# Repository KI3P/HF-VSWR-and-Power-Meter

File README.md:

# HF-VSWR-and-Power-Meter

System that measures the VSWR and power level of transmitter signals in the HF bands (3.5 MHz to 30 MHz) with better than 5% accuracy for VSWRs below 3.0. For a detailed explanation of its operation, see [its project page](https://ko4thb.github.io/2023/12/23/vswr_and_power_meter.html).

Gerbers were generated for manufacture by JLCPCB.

Credit: thanks to [G3TXQ](http://karinya.net/g3txq/swr_meter/) for sharing his SWR meter design and [schematic diagram](http://karinya.net/g3txq/swr_meter/schematic.jpg). Thanks to N7DDC for sharing the design of the [ATU-100 antenna tuner](https://github.com/Dfinitski/N7DDC-ATU-100-mini-and-extended-boards). And to W2AEW for his [excellent explanation](https://www.youtube.com/watch?v=byF1FLdbUiA) of how a directional coupler works. IN3OTD has an [online calculator](https://www.qsl.net/in3otd/parallr.html) for synthesizing arbitrary resistor values from standard value.  All these were tremendously helpful as I designed this VSWR meter.

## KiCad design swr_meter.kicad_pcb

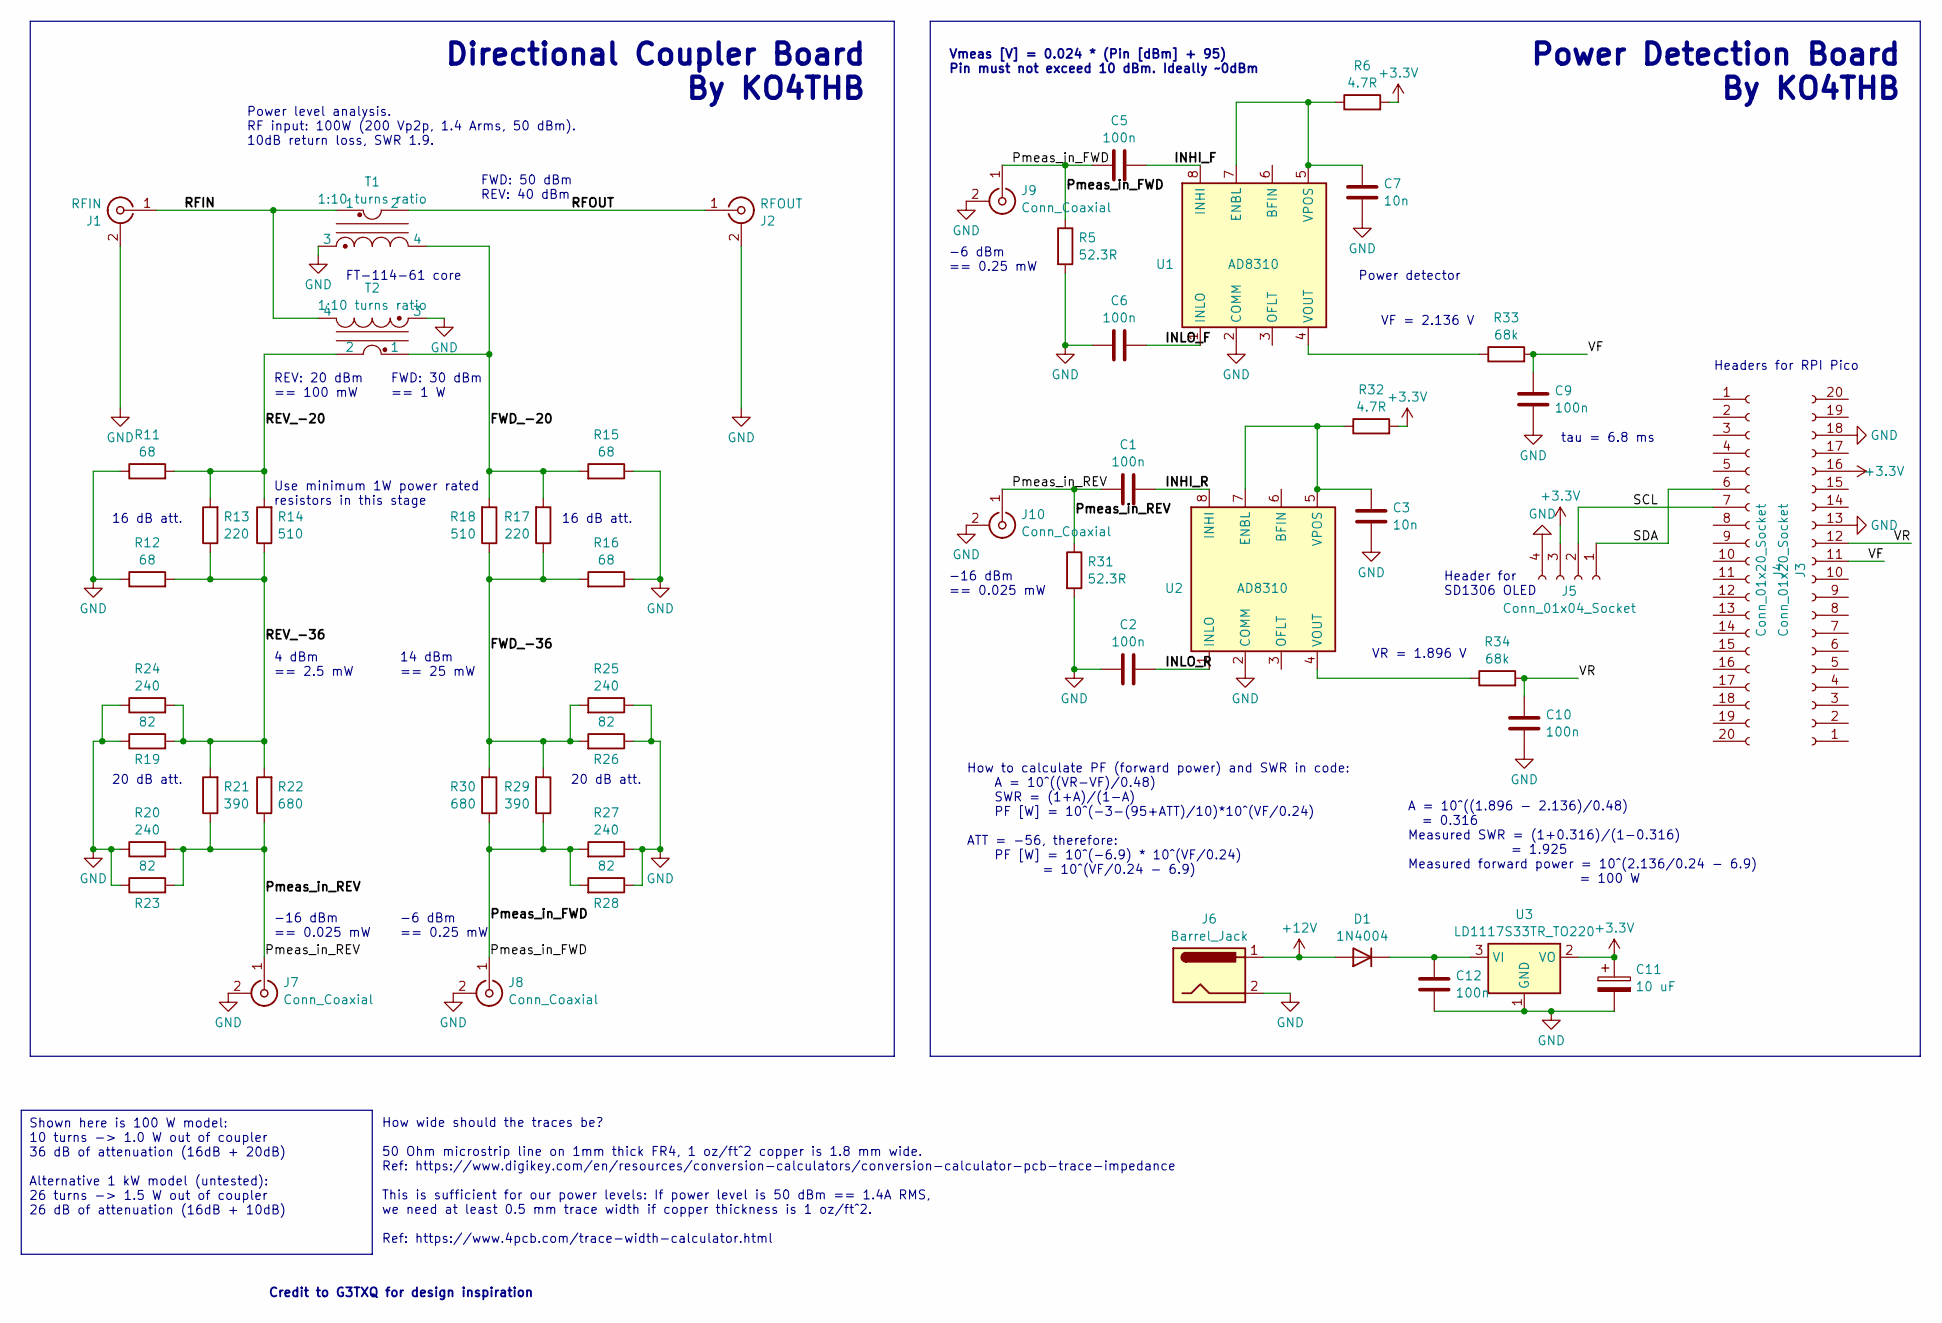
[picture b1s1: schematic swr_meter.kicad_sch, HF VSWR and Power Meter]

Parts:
C1, C2, C5, C6, C9, C10, C12: 100n; C_Disc_D9.0mm_W2.5mm_P5.00mm
C3, C7: 10n; C_Disc_D9.0mm_W2.5mm_P5.00mm
C11: 10 uF; CP_Radial_D6.3mm_P2.50mm
D1: 1N4004; D_DO-41_SOD81_P10.16mm_Horizontal
J1: RFIN; BNC_TEConnectivity_1478035_Horizontal
J2: RFOUT; BNC_TEConnectivity_1478035_Horizontal
J3, J4: Conn_01x20_Socket; PinHeader_1x20_P2.54mm_Vertical
J5: Conn_01x04_Socket; PinHeader_1x04_P2.54mm_Vertical
J6: Barrel_Jack; BarrelJack_Wuerth_6941xx301002
J7, J8, J9, J10: Conn_Coaxial; SMA_Amphenol_901-144_Vertical
R5, R31: 52.3R; R_Axial_DIN0207_L6.3mm_D2.5mm_P10.16mm_Horizontal
R6, R32: 4.7R; R_Axial_DIN0207_L6.3mm_D2.5mm_P10.16mm_Horizontal
R11, R12, R15, R16: 68; R_Axial_DIN0414_L11.9mm_D4.5mm_P15.24mm_Horizontal
R13, R17: 220; R_Axial_DIN0414_L11.9mm_D4.5mm_P15.24mm_Horizontal
R14, R18: 510; R_Axial_DIN0414_L11.9mm_D4.5mm_P15.24mm_Horizontal
R19, R23, R26, R28: 82; R_Axial_DIN0414_L11.9mm_D4.5mm_P15.24mm_Horizontal
R20, R24, R25, R27: 240; R_Axial_DIN0414_L11.9mm_D4.5mm_P15.24mm_Horizontal
R21, R29: 390; R_Axial_DIN0414_L11.9mm_D4.5mm_P15.24mm_Horizontal
R22, R30: 680; R_Axial_DIN0414_L11.9mm_D4.5mm_P15.24mm_Horizontal
R33, R34: 68k; R_Axial_DIN0207_L6.3mm_D2.5mm_P10.16mm_Horizontal
T1, T2: 1:10 turns ratio; Transformer_Toroid_Horizontal_D14.0mm_Amidon-T50
U1, U2: AD8310; MSOP-8_3x3mm_P0.65mm
U3: LD1117S33TR_TO220; TO-220-3_Vertical

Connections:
+3.3V: C11.1, J3.16, J5.3, R6.2, R32.2, U3.2 (VO)
+12V: D1.2 (A), J6.1
/FWD_-20: R15.2, R17.2, R18.2, T1.4, T2.1
/FWD_-36: R16.2, R17.1, R18.1, R25.2, R26.2, R29.2, R30.2
/INHI_F: C5.2, U1.8 (INHI)
/INHI_R: C1.2, U2.8 (INHI)
/INLO_F: C6.2, U1.1 (INLO)
/INLO_R: C2.2, U2.1 (INLO)
/Pmeas_in_FWD: C5.1, J8.1 (In), J9.1 (In), R5.1, R27.2, R28.2, R29.1, R30.1
/Pmeas_in_REV: C1.1, J7.1 (In), J10.1 (In), R20.2, R21.1, R22.1, R23.2, R31.1
/REV_-20: R11.2, R13.2, R14.2, T2.2
/REV_-36: R12.2, R13.1, R14.1, R19.2, R21.2, R22.2, R24.2
/RFIN: J1.1 (In), T1.1, T2.4
/RFOUT: J2.1 (In), T1.2
/SCL: J4.7, J5.2
/SDA: J4.6, J5.1
/VF: C9.2, J3.11, R33.2
/VR: C10.2, J3.12, R34.2
GND: C2.1, C3.1, C6.1, C7.1, C9.1, C10.1, C11.2, C12.1, J1.2 (Ext), J2.2 (Ext), J3.13, J3.18, J5.4, J6.2, J7.2 (Ext), J8.2 (Ext), J9.2 (Ext), J10.2 (Ext), R5.2, R11.1, R12.1, R15.1, R16.1, R19.1, R20.1, R23.1, R24.1, R25.1, R26.1, R27.1, R28.1, R31.2, T1.3, T2.3, U1.2 (COMM), U2.2 (COMM), U3.1 (GND)
unnamed: C12.2, D1.1 (K), U3.3 (VI)
unnamed: C7.2, R6.1, U1.5 (VPOS), U1.7 (ENBL)
unnamed: R33.1, U1.4 (VOUT)
unnamed: C3.2, R32.1, U2.5 (VPOS), U2.7 (ENBL)
unnamed: R34.1, U2.4 (VOUT)

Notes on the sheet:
Shown here is 100 W model: 10 turns -> 1.0 W out of coupler 36 dB of attenuation (16dB + 20dB) Alternative 1 kW model (untested): 26 turns -> 1.5 W out of coupler 26 dB of attenuation (16dB + 10dB)
-16 dBm == 0.025 mW
4 dBm == 2.5 mW
Power level analysis. RF input: 100W (200 Vp2p, 1.4 Arms, 50 dBm). 10dB return loss, SWR 1.9.
Power Detection Board By KO4THB
VR = 1.896 V
Use minimum 1W power rated resistors in this stage
FWD: 30 dBm == 1 W
20 dB att.
FWD: 50 dBm REV: 40 dBm
Headers for RPI Pico
tau = 6.8 ms
FT-114-61 core
Header for SD1306 OLED
14 dBm == 25 mW
-6 dBm == 0.25 mW
REV: 20 dBm == 100 mW
16 dB att.
How to calculate PF (forward power) and SWR in code: A = 10^((VR-VF)/0.48) SWR = (1+A)/(1-A) PF [W] = 10^(-3-(95+ATT)/10)*10^(VF/0.24) ATT = -56, therefore: PF [W] = 10^(-6.9) * 10^(VF/0.24) = 10^(VF/0.24 - 6.9)
Vmeas [V] = 0.024 * (Pin [dBm] + 95) Pin must not exceed 10 dBm. Ideally ~0dBm
VF = 2.136 V
Power detector
How wide should the traces be? 50 Ohm microstrip line on 1mm thick FR4, 1 oz/ft^2 copper is 1.8 mm wide. Ref: https://www.digikey.com/en/resources/conversion-calculators/conversion-calculator-pcb-trace-impedance This is sufficient for our power levels: If power level is 50 dBm == 1.4A RMS, we need 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
A = 10^((1.896 - 2.136)/0.48) = 0.316 Measured SWR = (1+0.316)/(1-0.316) = 1.925 Measured forward power = 10^(2.136/0.24 - 6.9) = 100 W
Directional Coupler Board By KO4THB
Credit to G3TXQ for design inspiration

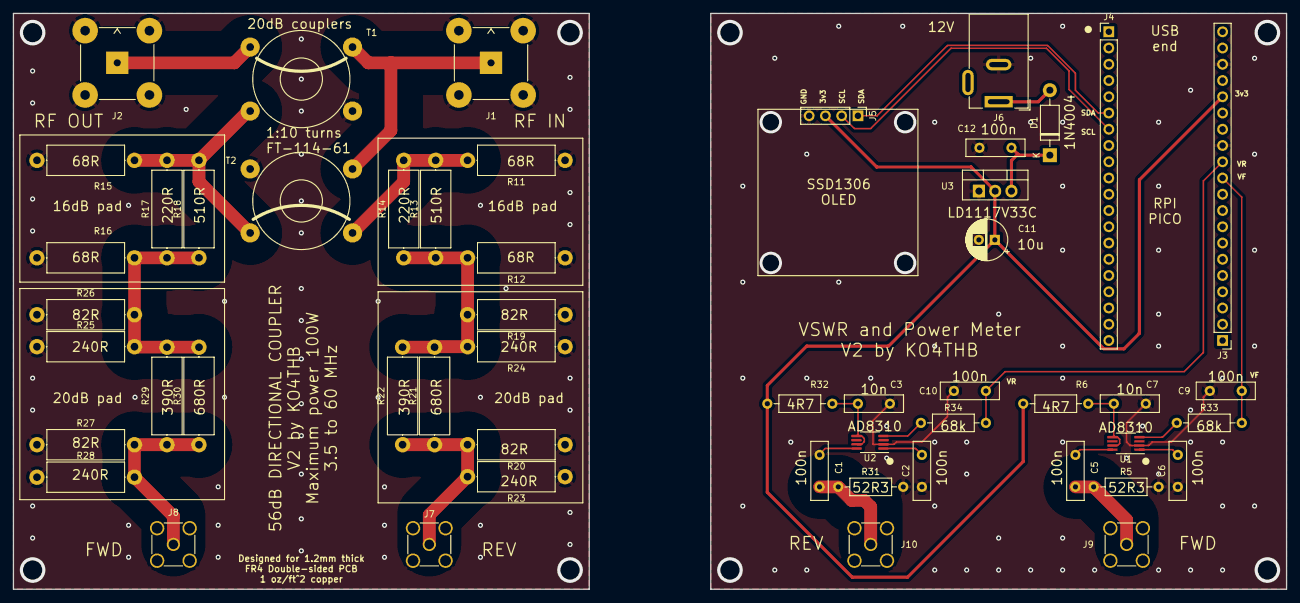
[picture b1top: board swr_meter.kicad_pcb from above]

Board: 2 copper layers, 199.0 x 90.0 mm, 52 parts (0 on the bottom side), 24 nets.

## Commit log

2023-12-23 Ready for release
